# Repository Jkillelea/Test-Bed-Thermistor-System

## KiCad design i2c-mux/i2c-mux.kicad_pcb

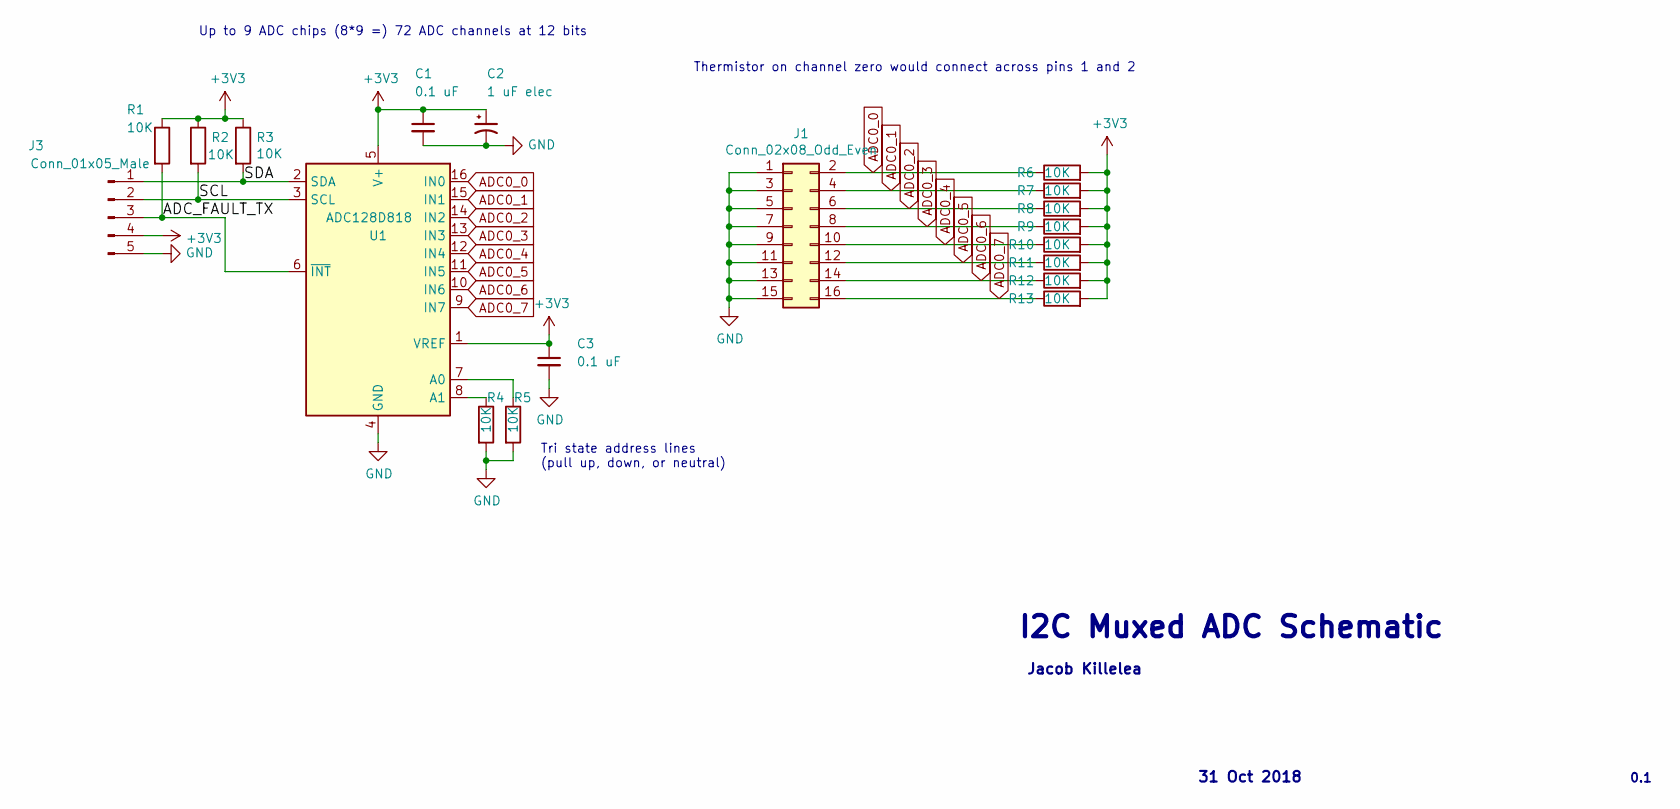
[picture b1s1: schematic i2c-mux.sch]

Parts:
C1, C3: 0.1 uF; C_Disc_D4.3mm_W1.9mm_P5.00mm
C2: 1 uF elec; CP_Radial_D4.0mm_P2.00mm
J1: Conn_02x08_Odd_Even; PinSocket_2x08_P2.54mm_Vertical
J3: Conn_01x05_Male; PinHeader_1x05_P2.54mm_Vertical
R1, R2, R3, R4, R5, R6, R7, R8, R9, R10, R11, R12, R13: 10K; R_Axial_DIN0207_L6.3mm_D2.5mm_P10.16mm_Horizontal
U1: ADC128D818; TSSOP-16_4.4x5mm_P0.65mm

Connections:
+3V3: C1.1, C2.1, C3.1, J3.4, R1.1, R2.1, R3.1, R6.2, R7.2, R8.2, R9.2, R10.2, R11.2, R12.2, R13.2, U1.1 (VREF), U1.5 (V+)
/ADC_FAULT_TX: J3.3, R1.2, U1.6 (~INT)
/SCL: J3.2, R2.2, U1.3 (SCL)
/SDA: J3.1, R3.2, U1.2 (SDA)
ADC0_0: J1.2, R6.1, U1.16 (IN0)
ADC0_1: J1.4, R7.1, U1.15 (IN1)
ADC0_2: J1.6, R8.1, U1.14 (IN2)
ADC0_3: J1.8, R9.1, U1.13 (IN3)
ADC0_4: J1.10, R10.1, U1.12 (IN4)
ADC0_5: J1.12, R11.1, U1.11 (IN5)
ADC0_6: J1.14, R12.1, U1.10 (IN6)
ADC0_7: J1.16, R13.1, U1.9 (IN7)
GND: C1.2, C2.2, C3.2, J1.1, J1.3, J1.5, J1.7, J1.9, J1.11, J1.13, J1.15, J3.5, R4.2, R5.2, U1.4 (GND)
unnamed: R4.1, U1.8 (A1)
unnamed: R5.1, U1.7 (A0)

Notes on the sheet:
Tri state address lines (pull up, down, or neutral)
Up to 9 ADC chips (8*9 =) 72 ADC channels at 12 bits
I2C Muxed ADC Schematic
Jacob Killelea
31 Oct 2018
0.1
Thermistor on channel zero would connect across pins 1 and 2

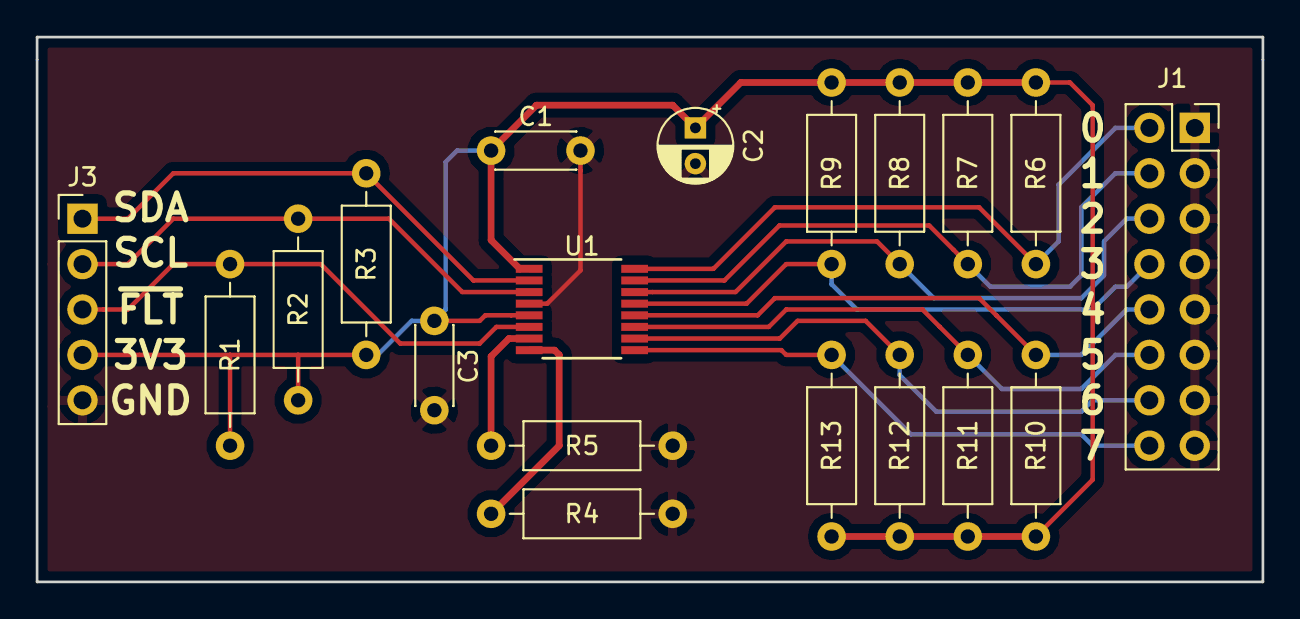
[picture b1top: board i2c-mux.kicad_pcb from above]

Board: 2 copper layers, 68.6 x 30.5 mm, 19 parts (0 on the bottom side), 15 nets.

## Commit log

2018-11-28 calculations
2018-11-28 i2c TI ADC128D818 PCB
2018-11-28 experimental idea for a single ADC chip pcb. Not going to be used
2018-11-28 delete
2018-11-28 move to make room for submodule
2018-11-28 del. Everything matches the submodule
2018-11-28 linewidth
2018-11-28 Error analysis
2018-11-28 plots
2018-11-30 Uncertainty and error analysis updates
2018-11-30 I don't even remember what's what anymore
